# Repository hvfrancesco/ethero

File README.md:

Ethero is an ENC28J60 based ethernet shield for Homino board.
Homino is an Arduino compatible board using Atmega328 microcontroller.

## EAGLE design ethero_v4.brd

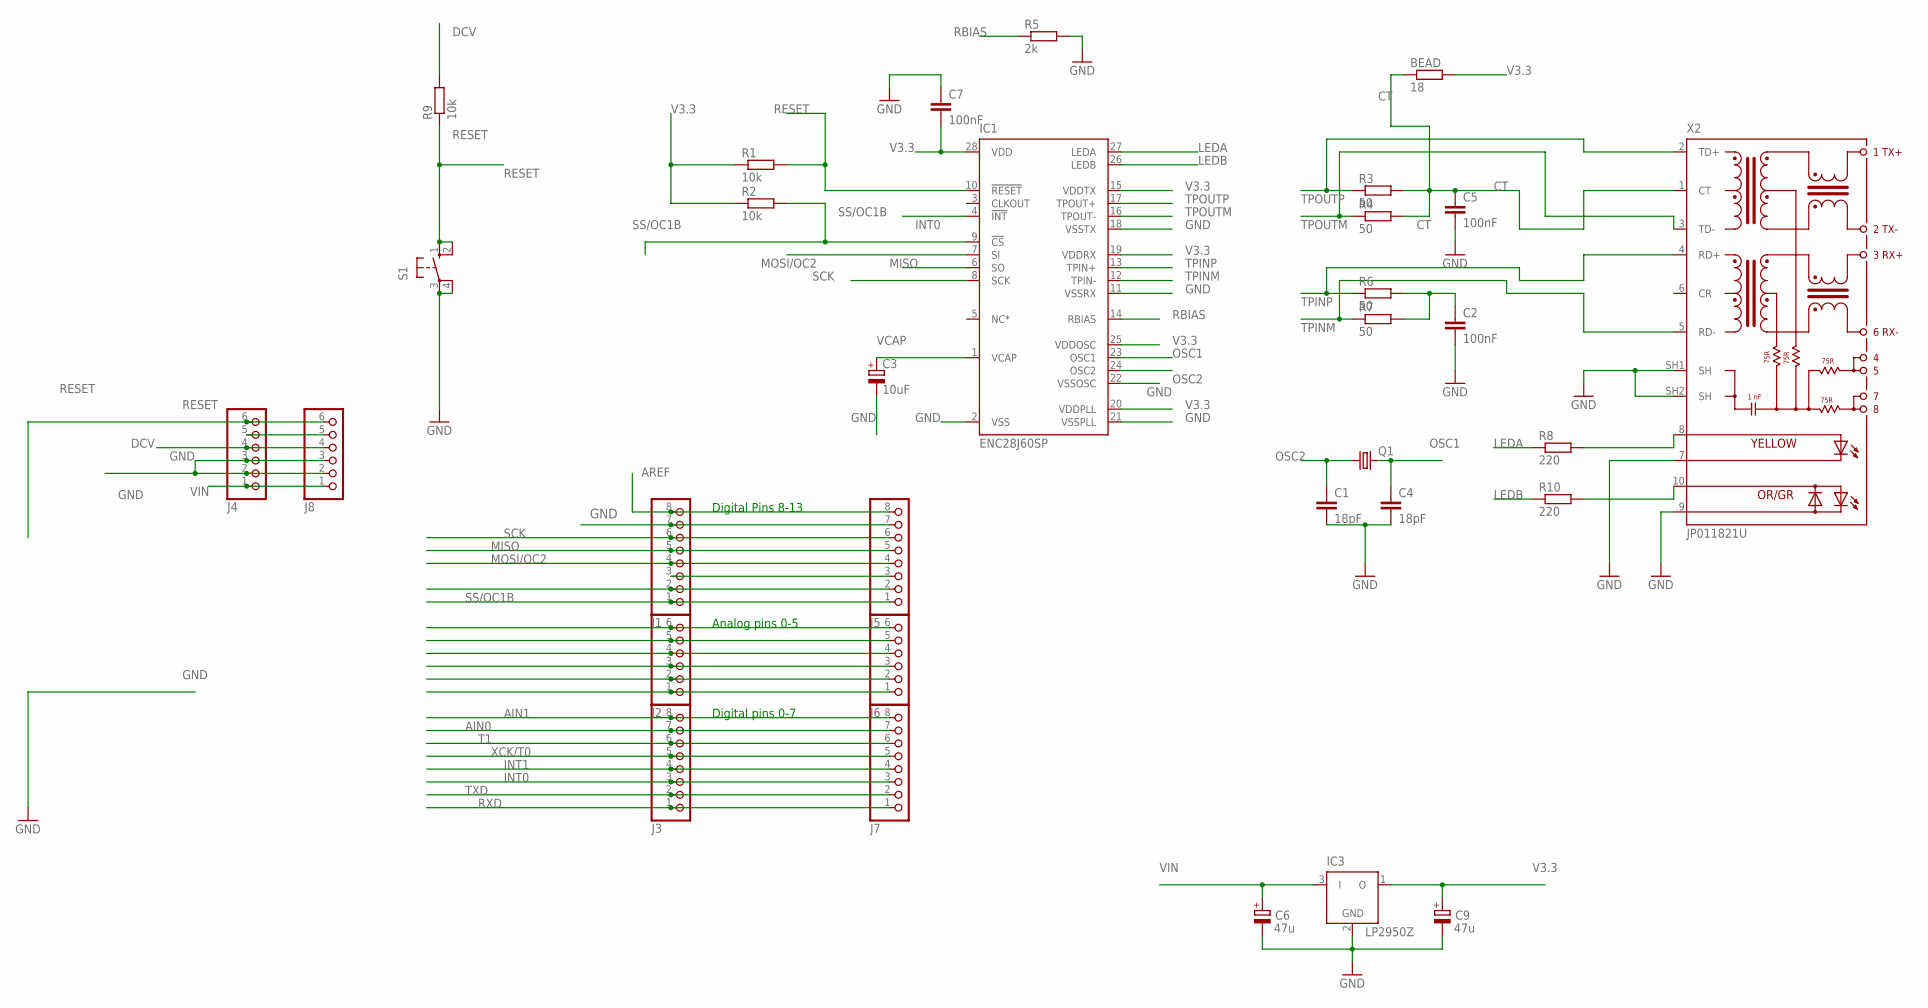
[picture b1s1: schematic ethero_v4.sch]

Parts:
BEAD: 18; 0204/7
C1, C4: 18pF; C025-025X050
C2, C5, C7: 100nF; C025-025X050
C3: 10uF; E5-5
C6, C9: 47u; E3,5-8
IC1: ENC28J60SP; DIL28-3
IC3: LP2950Z; TO92
J1, J3, J5, J7: PINHD-1X8; 1X08
J2, J4, J6, J8: PINHD-1X6; 1X06
Q1: CRYSTALHC18U-V; HC18U-V
R1, R2, R9: 10k; 0204/7
R3, R4, R6, R7: 50; 0204/7
R5: 2k; 0204/7
R8, R10: 220; 0204/7
S1: 10-XX; B3F-10XX
X2: JP011821U; JP

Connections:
AIN0: J3.7, J7.7
AIN1: J3.8, J7.8
AREF: J1.8, J5.8
CT: BEAD.1, C5.1, R3.2, R4.2, X2.1 (CT)
DCV: J4.4, J8.4, R9.2
GND: C1.2, C2.2, C3.-, C4.2, C5.2, C6.-, C7.1, C9.-, IC1.2 (VSS), IC1.11 (VSSRX), IC1.18 (VSSTX), IC1.21 (VSSPLL), IC1.22 (VSSOSC), IC3.2 (GND), J1.7, J4.2, J4.3, J5.7, J8.2, J8.3, R5.2, S1.3, S1.4 (P1), X2.7 (C-Y), X2.9 (A-O_C-G), X2.SH1 (SH), X2.SH2 (SH)
INT0: IC1.4 (!INT), J3.3, J7.3
INT1: J3.4, J7.4
LEDA: IC1.27 (LEDA), R8.1
LEDB: IC1.26 (LEDB), R10.1
MISO: IC1.6 (SO), J1.5, J5.5
MOSI/OC2: IC1.7 (SI), J1.4, J5.4
unnamed: J1.2, J5.2
unnamed: J4.5, J8.5
unnamed: C2.1, R6.2, R7.2
unnamed: J1.3, J5.3
unnamed: R8.2, X2.8 (A-Y)
unnamed: R10.2, X2.10 (C-O_A-G)
unnamed: J2.1, J6.1
unnamed: J2.2, J6.2
unnamed: J2.3, J6.3
unnamed: J2.4, J6.4
unnamed: J2.5, J6.5
unnamed: J2.6, J6.6
OSC1: C4.1, IC1.23 (OSC1), Q1.2
OSC2: C1.1, IC1.24 (OSC2), Q1.1
RBIAS: IC1.14 (RBIAS), R5.1
RESET: IC1.10 (!RESET), J4.6, J8.6, R1.2, R9.1, S1.1 (S), S1.2 (S1)
RXD: J3.1, J7.1
SCK: IC1.8 (SCK), J1.6, J5.6
SS/OC1B: IC1.9 (!CS), J1.1, J5.1, R2.2
T1: J3.6, J7.6
TPINM: IC1.12 (TPIN-), R7.1, X2.5 (RD-)
TPINP: IC1.13 (TPIN+), R6.1, X2.4 (RD+)
TPOUTM: IC1.16 (TPOUT-), R4.1, X2.3 (TD-)
TPOUTP: IC1.17 (TPOUT+), R3.1, X2.2 (TD+)
TXD: J3.2, J7.2
V3.3: BEAD.2, C7.2, C9.+, IC1.15 (VDDTX), IC1.19 (VDDRX), IC1.20 (VDDPLL), IC1.25 (VDDOSC), IC1.28 (VDD), IC3.1 (O), R1.1, R2.1
VCAP: C3.+, IC1.1 (VCAP)
VIN: C6.+, IC3.3 (I), J4.1, J8.1
XCK/T0: J3.5, J7.5

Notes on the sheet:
Analog pins 0-5
Digital Pins 8-13
Digital pins 0-7

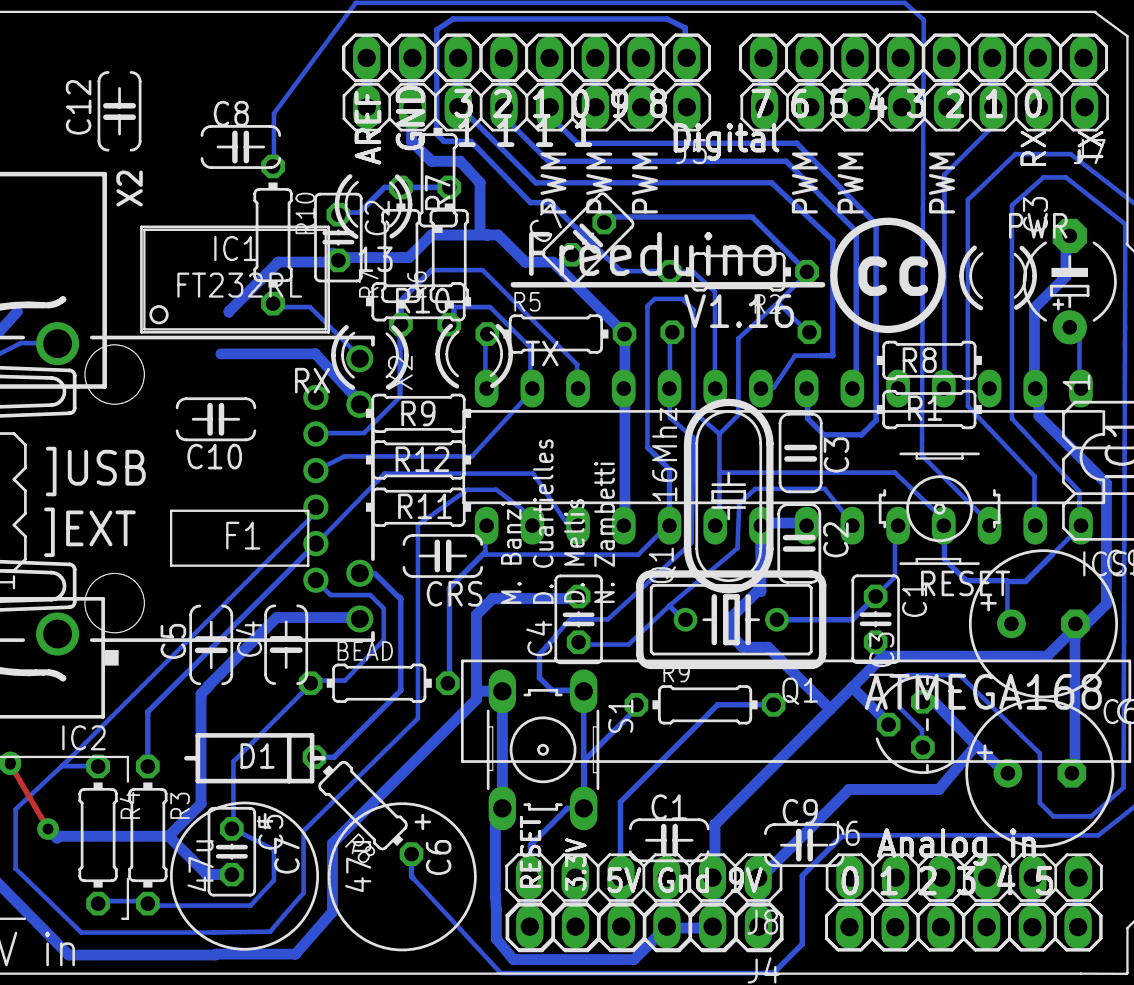
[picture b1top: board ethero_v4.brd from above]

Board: 2 copper layers, 32 parts (1 on the bottom side), 41 nets.

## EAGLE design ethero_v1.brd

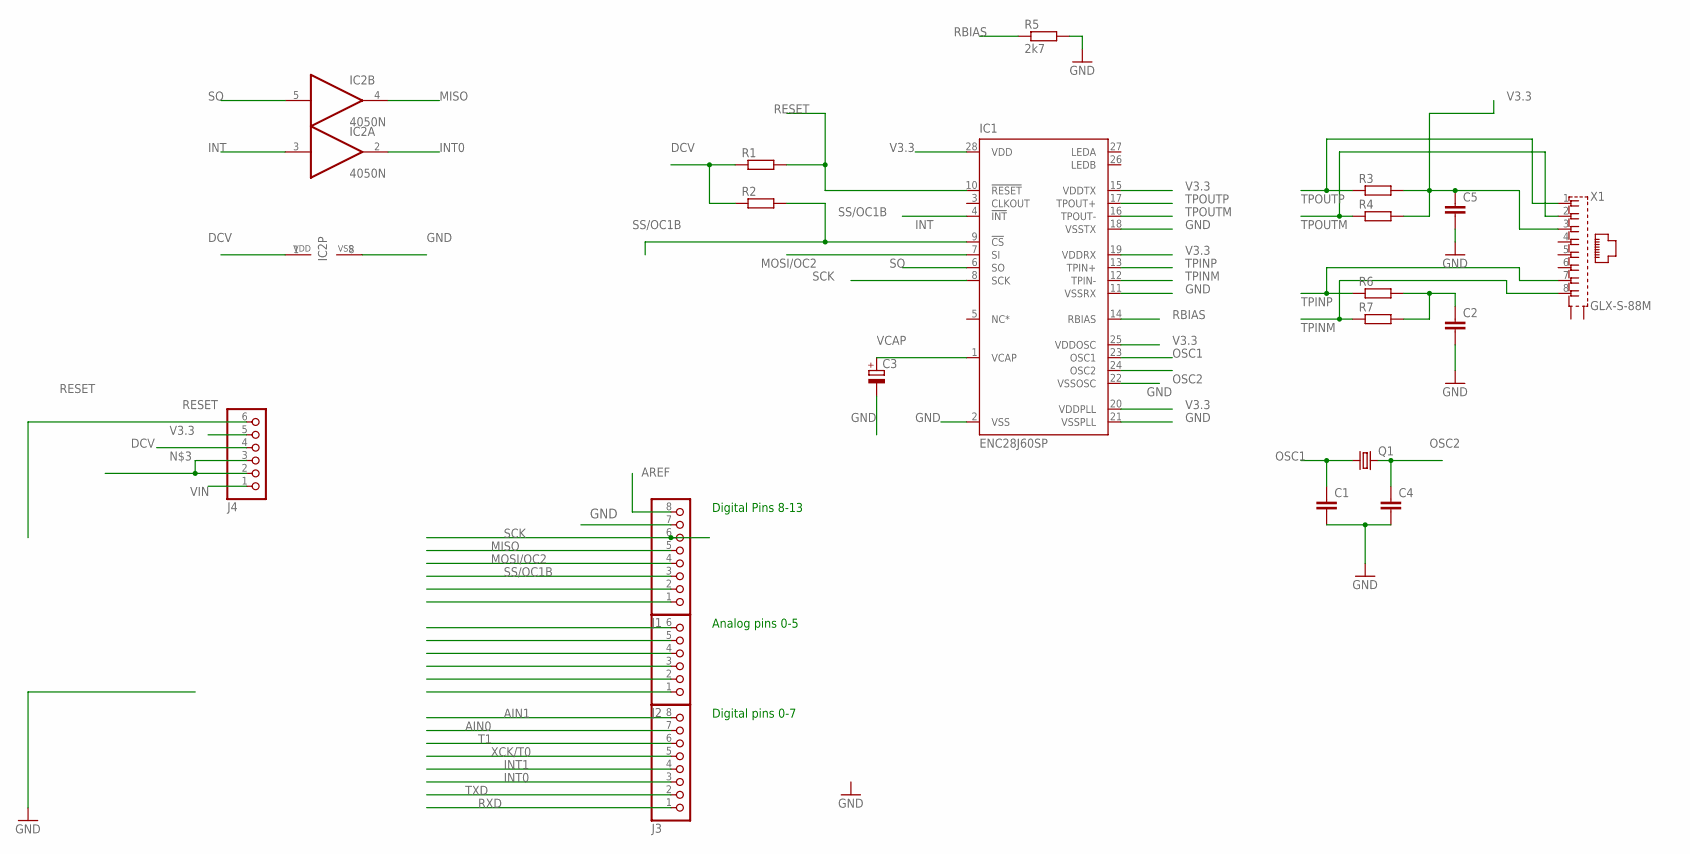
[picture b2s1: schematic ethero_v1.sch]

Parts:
C1, C2, C4, C5: C-EU025-025X050; C025-025X050
C3: CPOL-EUE5-5; E5-5
IC1: ENC28J60SP; DIL28-3
IC2: 4050N; DIL16
J1, J3: PINHD-1X8; 1X08
J2, J4: PINHD-1X6; 1X06
Q1: CRYSTALHC18U-V; HC18U-V
R1, R2, R3, R4, R6, R7: R-EU_0204/7; 0204/7
R5: 2k7; 0204/7
X1: GLX-S-88M

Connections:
AIN0: J3.7
AIN1: J3.8
AREF: J1.8
DCV: IC2.1 (VDD), J4.4, R1.1, R2.1
GND: C1.2, C2.2, C3.-, C4.2, C5.2, IC1.2 (VSS), IC1.11 (VSSRX), IC1.18 (VSSTX), IC1.21 (VSSPLL), IC1.22 (VSSOSC), IC2.8 (VSS), J1.7, R5.2
INT: IC1.4 (!INT), IC2.3 (I)
INT0: IC2.2 (O), J3.3
INT1: J3.4
MISO: IC2.4 (O), J1.5
MOSI/OC2: IC1.7 (SI), J1.4
unnamed: J4.2, J4.3
unnamed: C2.1, R6.2, R7.2
OSC1: C1.1, IC1.23 (OSC1), Q1.1
OSC2: C4.1, IC1.24 (OSC2), Q1.2
RBIAS: IC1.14 (RBIAS), R5.1
RESET: IC1.10 (!RESET), J4.6, R1.2
RXD: J3.1
SCK: IC1.8 (SCK), J1.6
SO: IC1.6 (SO), IC2.5 (I)
SS/OC1B: IC1.9 (!CS), J1.3, R2.2
T1: J3.6
TPINM: IC1.12 (TPIN-), R7.1, X1.8
TPINP: IC1.13 (TPIN+), R6.1, X1.7
TPOUTM: IC1.16 (TPOUT-), R4.1, X1.2
TPOUTP: IC1.17 (TPOUT+), R3.1, X1.1
TXD: J3.2
V3.3: C5.1, IC1.15 (VDDTX), IC1.19 (VDDRX), IC1.20 (VDDPLL), IC1.25 (VDDOSC), IC1.28 (VDD), J4.5, R3.2, R4.2, X1.3
VCAP: C3.+, IC1.1 (VCAP)
VIN: J4.1
XCK/T0: J3.5

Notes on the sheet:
Analog pins 0-5
Digital Pins 8-13
Digital pins 0-7

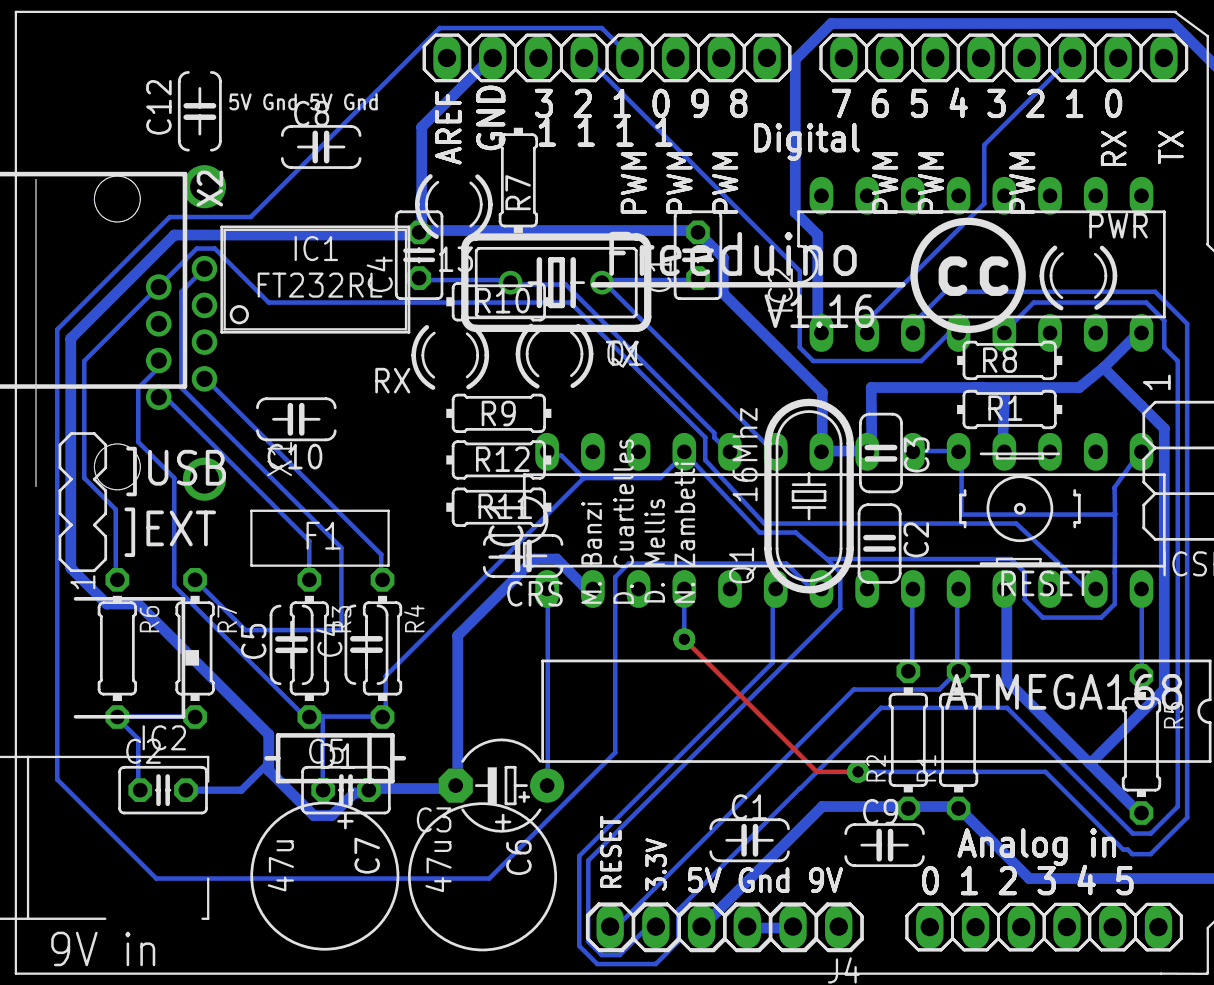
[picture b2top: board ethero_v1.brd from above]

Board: 2 copper layers, 20 parts (0 on the bottom side), 21 nets.

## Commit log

2013-07-02 added basic info to README
2013-07-03 added non inverting buffer for level switching
2013-07-10 first draft of prototype v.2
2013-07-10 started routing v.2
2013-07-12 version 3 ready for testing
2013-07-12 images of finished prototype
2013-07-12 cleaned tree
2013-07-12 removed example schematics
2013-07-16 revision 4, added female headers
